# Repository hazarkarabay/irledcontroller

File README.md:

# irledcontroller
Simple LED Strip controller with IR remote control.

This project controls brightness of single LED strip from an IR remote. Currently it is using RC6 protocol because I have a MCE remote nearby. Thanks to [IRLib2](https://github.com/cyborg5/IRLib2), it can be configured to work with nearly any IR remote. 

Hardware
--------

A single-sided, toner transfer friendly PCB created for this project. Schematic and board files included in Hardware folder. You'll need [EAGLE](http://www.autodesk.com/products/eagle/free-download) for opening them.  
ATMega328 receives and decodes IR signals, reads an LDR to decide its status while first power-on and PWMs a N-Channel MOSFET to control lights. You'll need supply required voltage for your LED strip to this board. LED strips are generally 12V and board will work with 9-25V LED strips. 30V is absolute maximum for on-board regulator. On-board power MOSFET AO3406 can support up to 3.5A load, please check your strips' power requirement.  
Board also can support Arduino environment (supports DTS reset).

Software
--------

Software written in Arduino environment and commented heavily. Currently it uses 3 IR remote buttons to toggle light and increase/decrease brightness. It uses psychometric lightness formula (CIE 1931) for adjusting brightness and can fade in/out very smoothly (to human eye).  
Currently it uses Timer1 at 12bit mode for PWM. ATmega328 can switch at ~4kHz on this mode. Faster PWM frequencies needs reduced duty cycle resolution. 

Things to know
--------------

Since switching frequency of 4kHz is in audible range, this can leads audible noise. I did not hear anything in my application but you must aware of that.  
The board has an LDR and it only used in first power up. If the ambient light is low while powering on, it will fade lights to %100. After first start-up LDR status is ignored currently (no auto lights-on at night, sorry).  
ATMega328 is way overkill for this kind of project but I don't have any ATTinys in my hand. Because I have relatively high computing power at my hand, I didn't used lookup tables for CIE 1931 calculation, which deals with floats and exponentials. You probably want use a lookup table if you need to use ATTiny.  
If you want use serial debug output, uncomment `#define DEBUG` at line 21.

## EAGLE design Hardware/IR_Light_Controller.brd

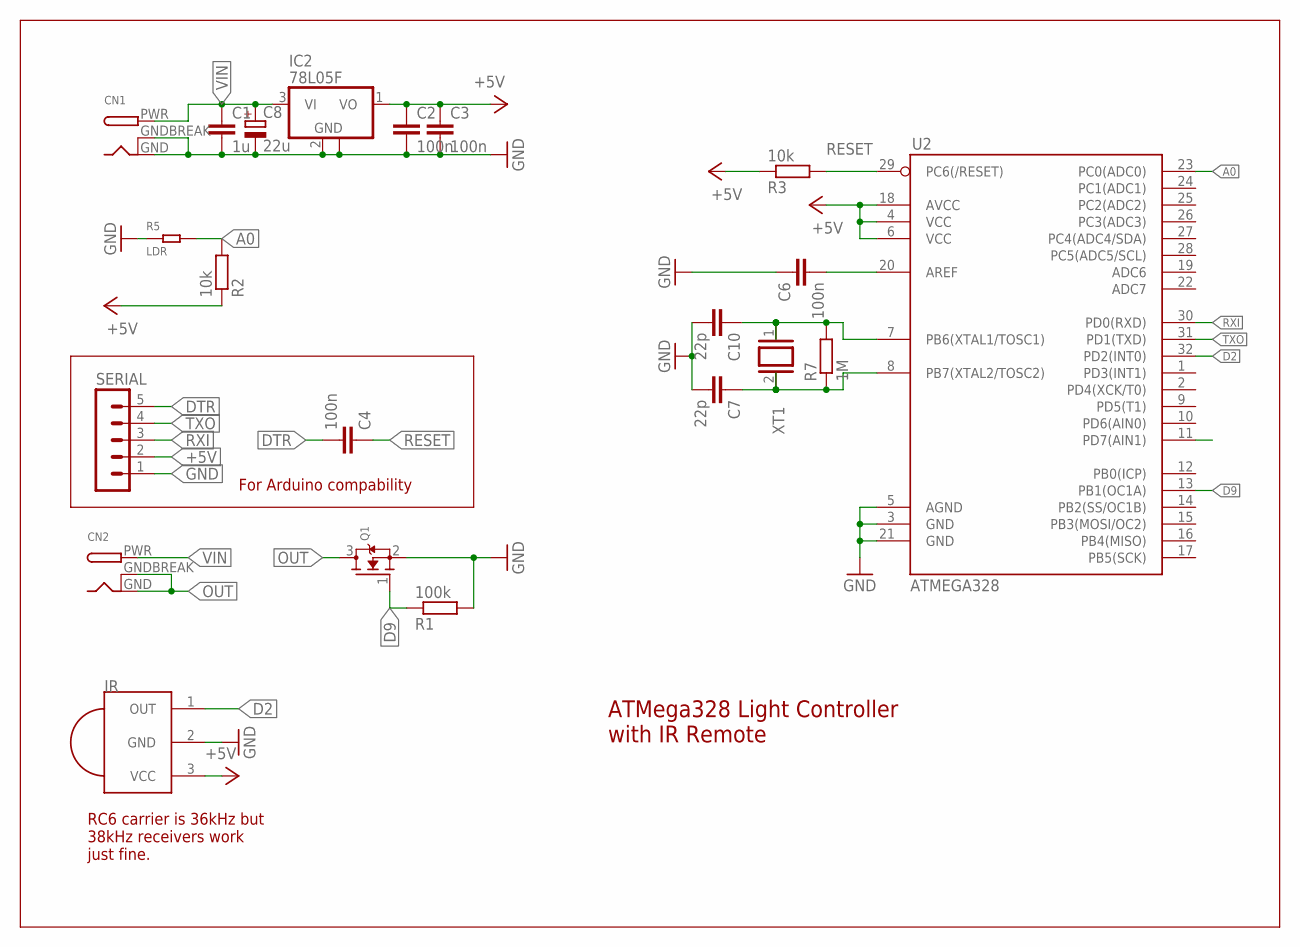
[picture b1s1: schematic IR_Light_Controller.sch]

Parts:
C1: 1u; C0805
C2, C3: 100n; C0805
C4, C6: 100n; C0805K
C7, C10: 22p; C0805K
C8: 22u; E2-4
CN1, CN2: DCBARRELPTH; DCJACK_2MM_PTH
IC2: 78L05F; SOT89
IR: PNA460XM
Q1: MOSFET-NWAVE; SOT23-W
R1: 100k; M0805
R2, R3: 10k; M0805
R5: LDR; PR-2.8-4.2X4.9MM
R7: 1M; M0805
SERIAL: MA05-1
U2: ATMEGA328; TQFP32-08
XT1: XTAL/S; QS

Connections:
+5V: C2.1, C3.1, IC2.1 (VO), IR.3 (VCC), R2.1, R3.1, SERIAL.2, U2.4 (VCC), U2.6 (VCC), U2.18 (AVCC)
A0: R2.2, R5.2, U2.23 (PC0(ADC0))
AREF: C6.2, U2.20 (AREF)
D2: IR.1 (OUT), U2.32 (PD2(INT0))
D7: U2.11 (PD7(AIN1))
D9: Q1.1 (G), R1.1, U2.13 (PB1(OC1A))
DTR: C4.2, SERIAL.5
GND: C1.2, C2.2, C3.2, C6.1, C7.2, C8.-, C10.2, CN1.GND, CN1.GNDBREAK, IC2.2 (GND), IC2.2@1 (GND), IR.2 (GND), Q1.2 (S), R1.2, R5.1, SERIAL.1, U2.3 (GND), U2.5 (AGND), U2.21 (GND)
OUT: CN2.GND, CN2.GNDBREAK, Q1.3 (D)
RESET: C4.1, R3.2, U2.29 (PC6(/RESET))
RXI: SERIAL.3, U2.30 (PD0(RXD))
TXO: SERIAL.4, U2.31 (PD1(TXD))
VIN: C1.1, C8.+, CN1.PWR, CN2.PWR, IC2.3 (VI)
XT1: C10.1, R7.2, U2.7 (PB6(XTAL1/TOSC1)), XT1.1
XT2: C7.1, R7.1, U2.8 (PB7(XTAL2/TOSC2)), XT1.2

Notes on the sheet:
RC6 carrier is 36kHz but 38kHz receivers work just fine.
ATMega328 Light Controller with IR Remote
For Arduino compability

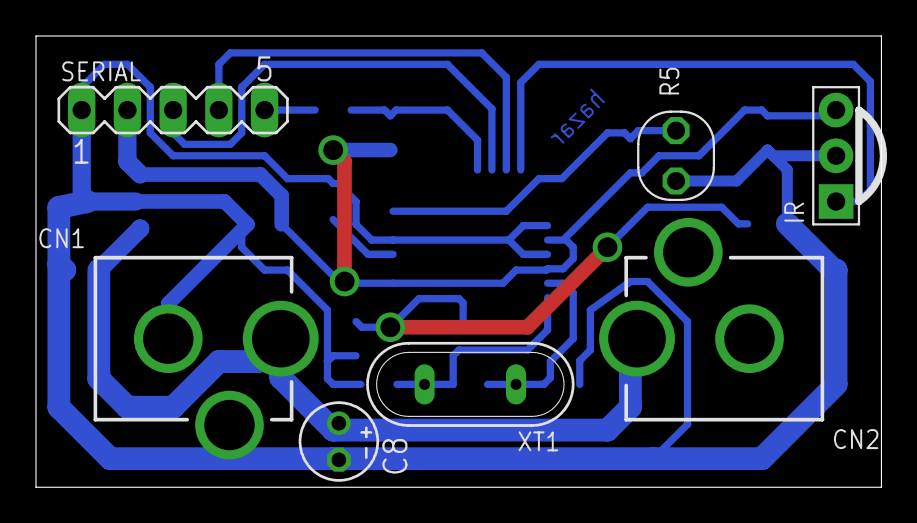
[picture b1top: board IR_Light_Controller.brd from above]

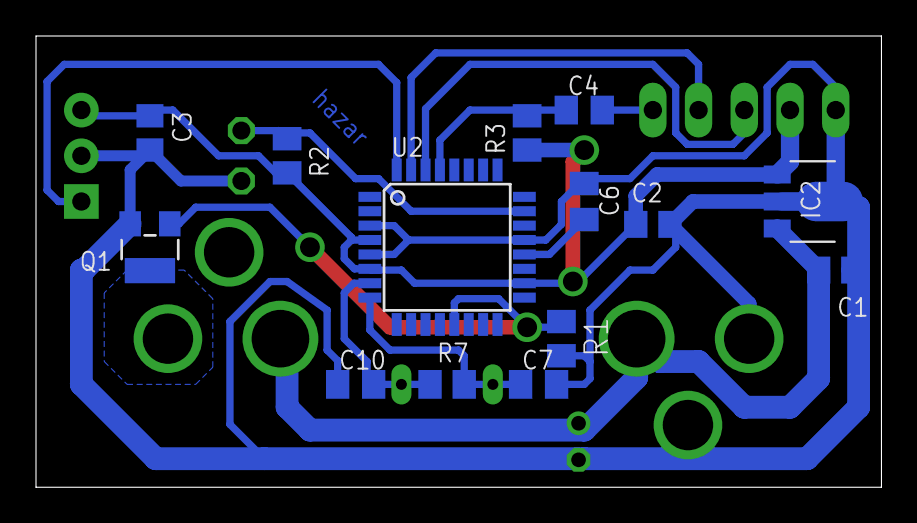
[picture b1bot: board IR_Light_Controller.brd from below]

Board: 2 copper layers, 47.0 x 25.1 mm, 21 parts (14 on the bottom side), 14 nets.

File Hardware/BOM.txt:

Qty Value     Device                     Package          Parts    Description                          
2             DCBARRELPTH                DCJACK_2MM_PTH   CN1, CN2 2.0mm DC Barrel Jack                 
1             MA05-1                     MA05-1           SERIAL   PIN HEADER                           
1             AO3406		         SOT23-W          Q1       N-Channel Mosfet                     
1             XTAL/S                     QS               XT1      CRYSTAL                              
1   100k      R-EU_M0805                 M0805            R1       RESISTOR, European symbol            
2   100n      C-EUC0805                  C0805            C2, C3,  CAPACITOR, European symbol
							  C4, C6              
2   10k       R-EU_M0805                 M0805            R2, R3   RESISTOR, European symbol            
1   1M        R-EU_M0805                 M0805            R7       RESISTOR, European symbol            
1   1u        C-EUC0805                  C0805            C1       CAPACITOR, European symbol           
2   22p       C-EUC0805K                 C0805K           C7, C10  CAPACITOR, European symbol           
1   22u       CPOL-EUE2-4                E2-4             C8       POLARIZED CAPACITOR, European symbol 
1   78L05F    78L05F                     SOT89            IC2      POSITOIV-VOLTAGE REGULATORS          
1   ATMEGA328 ATMEGA168                  TQFP32-08        U2                                            
1   LDR       DIP-RES-LDR(2P-D2.3X3.7MM) PR-2.8-4.2X4.9MM R5       314120003                            
1   PNA460XM  PNA460XM                   PNA460XM         IR       IR 36KHz receiver

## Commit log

2017-04-07 :circus_tent: Added .gitattributes & .gitignore files
2017-04-07 BOM and Datasheets
2017-04-09 IR lockup workaround and reorganization for Arduino IDE
    Workaround for #1 and file reorganization required for Arduino IDE.
